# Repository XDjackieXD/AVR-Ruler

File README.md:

A simple Ruler with an USBtinyISP programmer or development platform.
More Info at http://hackaday.io/project/938-Tiny-Ruler

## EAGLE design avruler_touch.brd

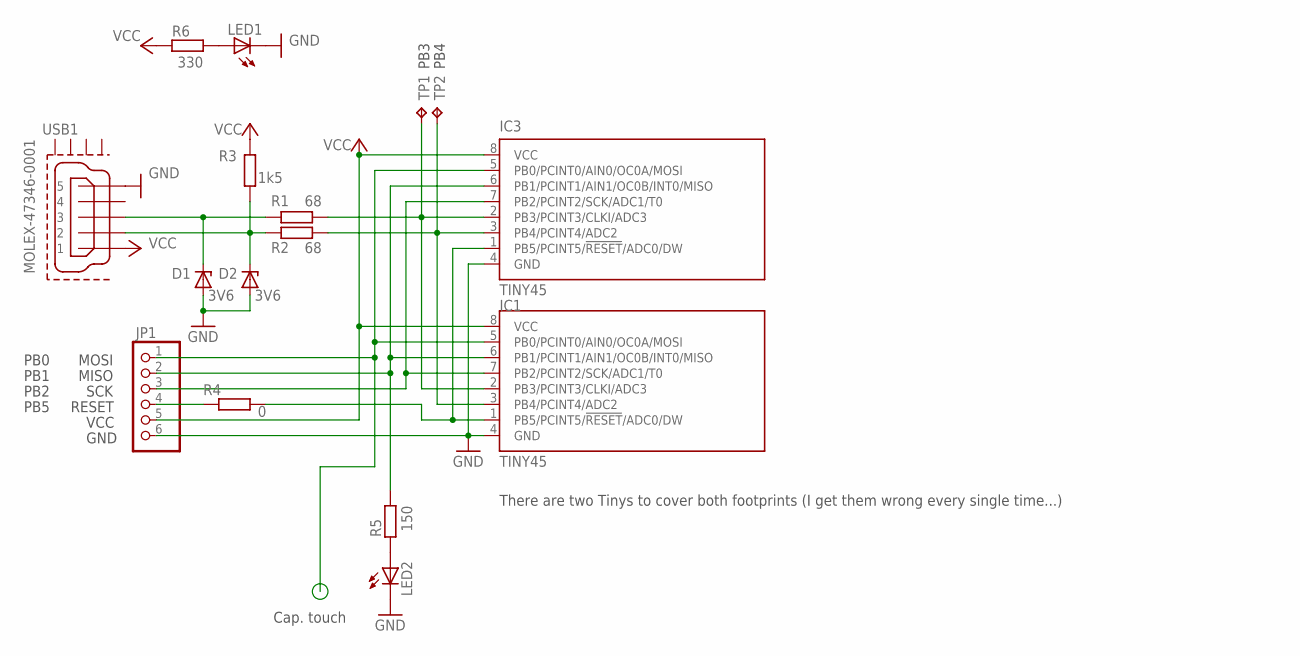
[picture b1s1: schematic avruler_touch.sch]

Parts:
D1, D2: 3V6; SOD80C
IC1: TINY45; 8S1
IC3: TINY45; 8S2
JP1: PINHD-1X6/90; 1X06/90
LED1, LED2: LEDCHIPLED_1206; CHIPLED_1206
R1, R2: 68; M1206
R3: 1k5; M1206
R4: 0; M1206
R5: 150; M1206
R6: 330; M1206
TP1, TP2: TPTP14SQ; TP14SQ
USB1: MOLEX-47346-0001; MOLEX-47364-0001

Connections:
GND: D1.A, D2.A, IC1.4 (GND), IC3.4 (GND), JP1.6, LED1.C, LED2.C, USB1.5
unnamed: IC1.1 (PB5/PCINT5/!RESET!/ADC0/DW), IC3.1 (PB5/PCINT5/!RESET!/ADC0/DW), R4.2
unnamed: IC1.2 (PB3/PCINT3/CLKI/ADC3), IC3.2 (PB3/PCINT3/CLKI/ADC3), R1.1, TP1.TP
unnamed: IC1.3 (PB4/PCINT4/ADC2), IC3.3 (PB4/PCINT4/ADC2), R2.1, TP2.TP
unnamed: IC1.5 (PB0/PCINT0/AIN0/OC0A/MOSI), IC3.5 (PB0/PCINT0/AIN0/OC0A/MOSI), JP1.1
unnamed: IC1.6 (PB1/PCINT1/AIN1/OC0B/INT0/MISO), IC3.6 (PB1/PCINT1/AIN1/OC0B/INT0/MISO), JP1.2, R5.1
unnamed: IC1.7 (PB2/PCINT2/SCK/ADC1/T0), IC3.7 (PB2/PCINT2/SCK/ADC1/T0), JP1.3
unnamed: D2.C, R2.2, R3.2, USB1.2
unnamed: D1.C, R1.2, USB1.3
unnamed: JP1.4, R4.1
unnamed: LED1.A, R6.1
unnamed: LED2.A, R5.2
VCC: IC1.8 (VCC), IC3.8 (VCC), JP1.5, R3.1, R6.2, USB1.1

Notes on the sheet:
There are two Tinys to cover both footprints (I get them wrong every single time...)
GND
VCC
RESET
SCK
MISO
MOSI
PB0
PB1
PB2
PB5
PB3
PB4
Cap. touch

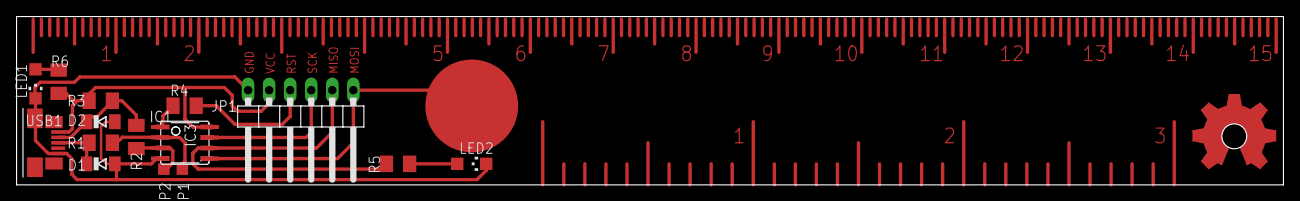
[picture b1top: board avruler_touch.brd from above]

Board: 2 copper layers, 152.9 x 20.3 mm, 17 parts (0 on the bottom side), 13 nets.

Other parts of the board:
U$1: OSHW_FILLX350_NOTEXT

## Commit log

2014-04-28 first commit - added schematic, board and readme
2014-04-28 updated README.md to match hackaday.io link
2014-04-28 swapped VCC and RESET on the pinheader
2014-04-29 added version with touch sensor and programmable led
2015-04-04 add a CC BY-SA License
